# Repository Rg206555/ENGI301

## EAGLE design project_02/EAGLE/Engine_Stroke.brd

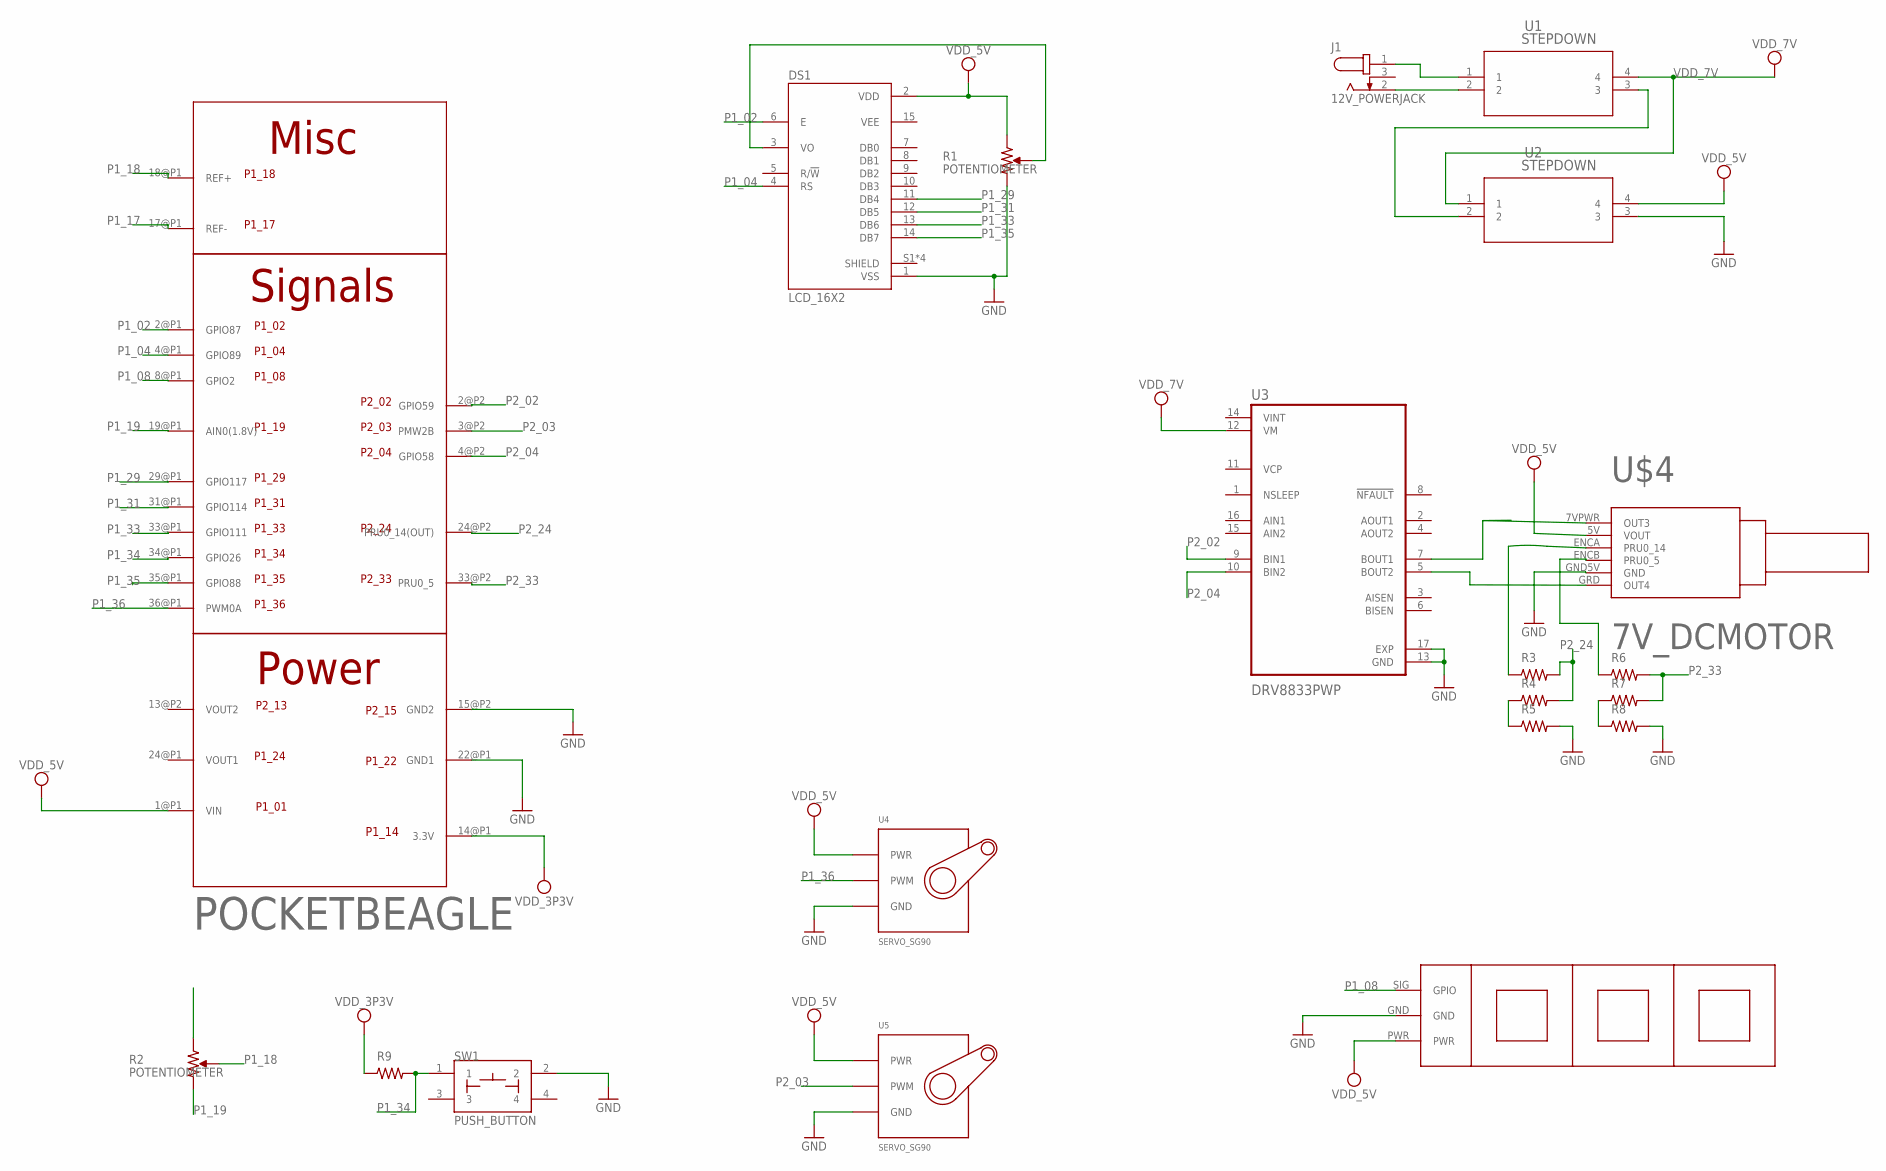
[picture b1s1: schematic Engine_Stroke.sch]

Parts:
DS1: LCD_16X2; LCD_RC1602B-BIW-CSV
J1: 12V_POWERJACK; CUI_PJ-102BH
R1, R2: POTENTIOMETER; POT-PO90S
R3, R4, R5, R6, R7, R8, R9: R_R0603; R0603
SW1: PUSH_BUTTON; BUTTON_12.5MM
U1, U2: STEPDOWN; IC4_DFR0067_DFR
U3: DRV8833PWP; IC_DRV8833PWP
U4, U5: SERVO_SG90; SERVO-X1
U$1: POCKETBEAGLE
U$3: RGB_LED_STRIP; LED_STRIP
U$4: 7V_DCMOTOR

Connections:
GND: DS1.1 (VSS), R1.CW, R5.2, R8.2, SW1.2, U2.3, U3.13 (GND), U3.17 (EXP), U4.GND, U5.GND, U$1.15@P2 (GND2), U$1.22@P1 (GND1), U$3.GND, U$4.GND5V (GND)
unnamed: J1.1, U1.1
unnamed: J1.2, U1.2
unnamed: U1.3, U2.2
unnamed: U3.7 (BOUT1), U$4.7VPWR (OUT3)
unnamed: U3.5 (BOUT2), U$4.GRD (OUT4)
unnamed: R3.1, U$4.ENCA (PRU0_14)
unnamed: R4.1, R5.1
unnamed: DS1.3 (VO), R1.S
unnamed: R6.1, U$4.ENCB (PRU0_5)
unnamed: R7.1, R8.1
P1_02: DS1.6 (E), U$1.2@P1 (GPIO87)
P1_04: DS1.4 (RS), U$1.4@P1 (GPIO89)
P1_08: U$1.8@P1 (GPIO2), U$3.SIG (GPIO)
P1_17: R2.CCW, U$1.17@P1 (REF-)
P1_18: R2.S, U$1.18@P1 (REF+)
P1_19: R2.CW, U$1.19@P1 (AIN0(1.8V))
P1_29: DS1.11 (DB4), U$1.29@P1 (GPIO117)
P1_31: DS1.12 (DB5), U$1.31@P1 (GPIO114)
P1_33: DS1.13 (DB6), U$1.33@P1 (GPIO111)
P1_34: R9.2, SW1.1, U$1.34@P1 (GPIO26)
P1_35: DS1.14 (DB7), U$1.35@P1 (GPIO88)
P1_36: U4.SIG (PWM), U$1.36@P1 (PWM0A)
P2_02: U3.9 (BIN1), U$1.2@P2 (GPIO59)
P2_03: U5.SIG (PWM), U$1.3@P2 (PMW2B)
P2_04: U3.10 (BIN2), U$1.4@P2 (GPIO58)
P2_24: R3.2, R4.2, U$1.24@P2 (PRU0_14(OUT))
P2_33: R6.2, R7.2, U$1.33@P2 (PRU0_5)
VDD_3P3V: R9.1, U$1.14@P1 (3.3V)
VDD_5V: DS1.2 (VDD), R1.CCW, U2.4, U3.12 (VM), U4.PWR, U5.PWR, U$1.1@P1 (VIN), U$3.PWR, U$4.5V (VOUT)
VDD_7V: U1.4, U2.1
VINT: U3.14 (VINT)

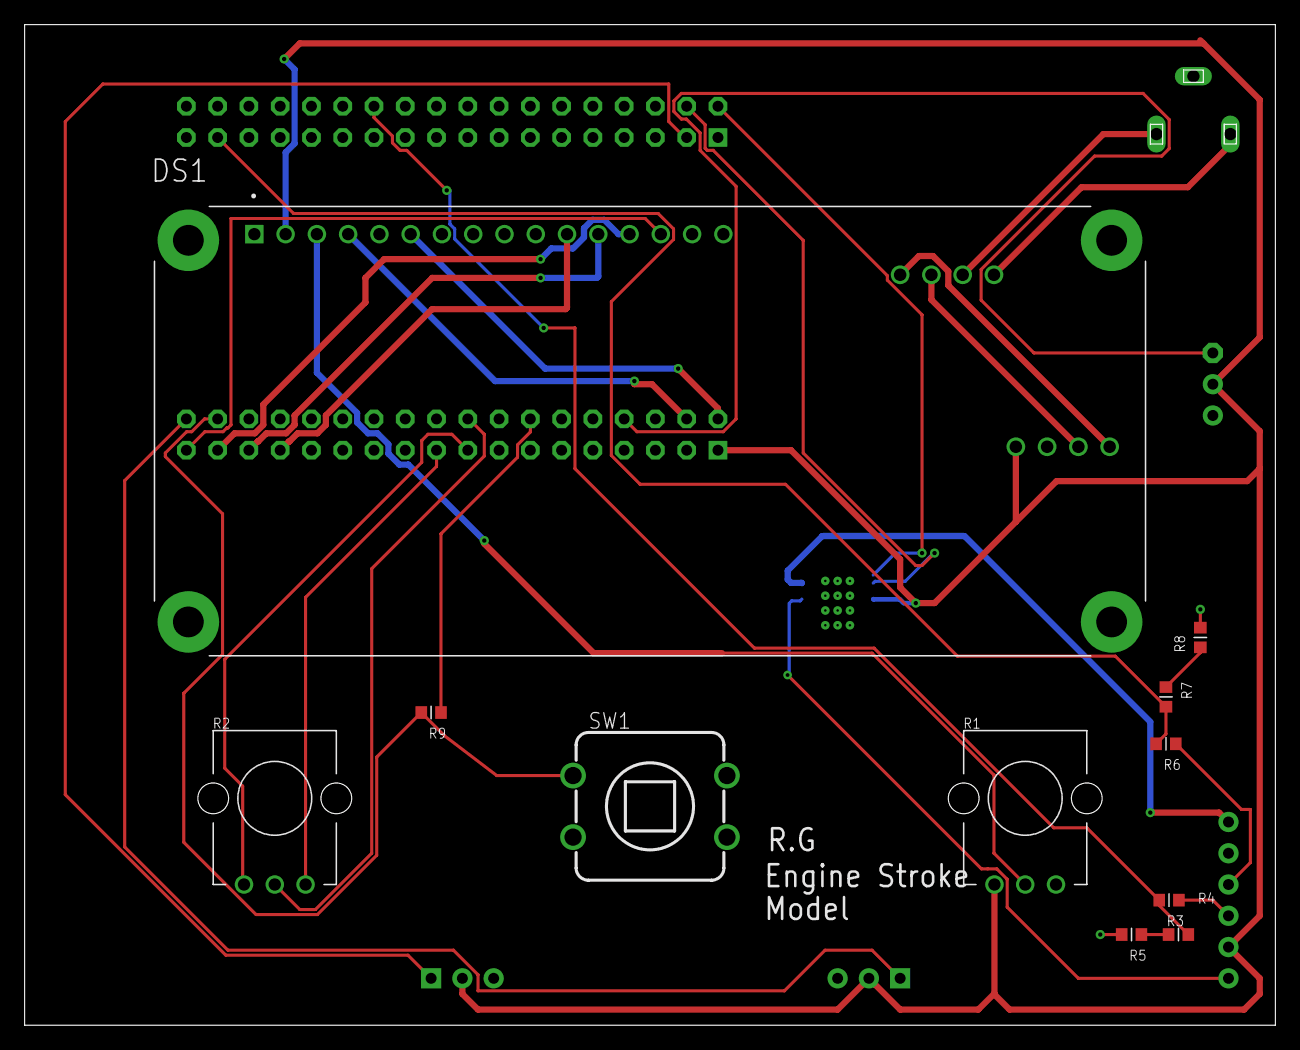
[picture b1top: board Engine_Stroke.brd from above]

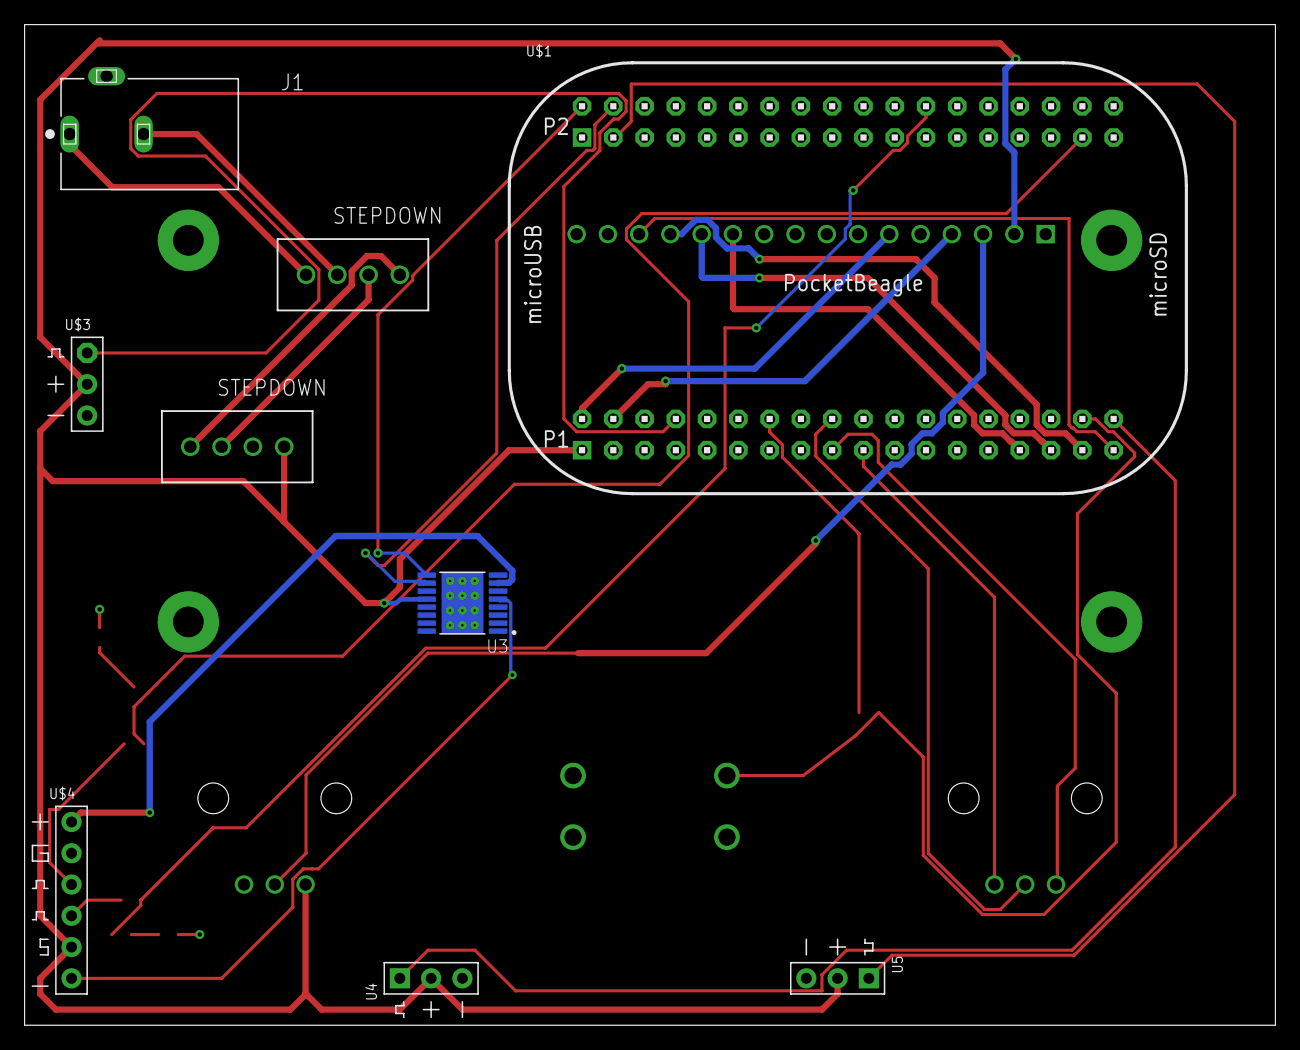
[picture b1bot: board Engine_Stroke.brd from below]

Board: 2 copper layers, 101.6 x 81.3 mm, 20 parts (9 on the bottom side), 31 nets.

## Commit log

2022-02-15 Adding USR3 file
2022-02-16 simple_calc.py
2022-05-04 Create EAGLE
2022-05-04 Create docs
2022-05-04 Create MFG

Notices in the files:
parts and their libraries:
COPYRIGHT: Copyright (C) 2022 Ultra Librarian. All rights reserved.
